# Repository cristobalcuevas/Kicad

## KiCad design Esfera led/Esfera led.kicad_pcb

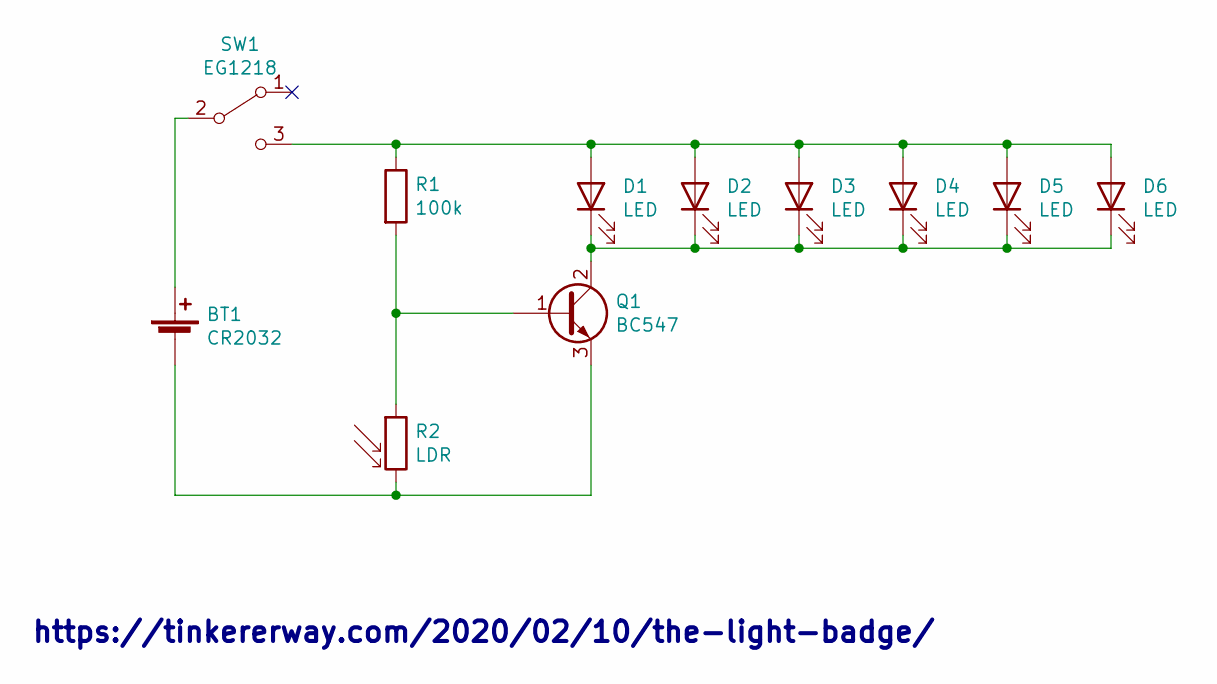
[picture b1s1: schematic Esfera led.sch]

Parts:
BT1: CR2032; BatteryHolder_Keystone_1058_1x2032
D1, D2, D3, D4, D5, D6: LED; LED_1206_3216Metric_Pad1.42x1.75mm_HandSolder
Q1: BC547; TO-92L_Inline
R1: 100k; R_1206_3216Metric_Pad1.42x1.75mm_HandSolder
R2: LDR; R_LDR_5.1x4.3mm_P3.4mm_Vertical
SW1: EG1218

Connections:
unnamed: BT1.1 (+), SW1.2 (B)
unnamed: BT1.2 (-), Q1.3 (E), R2.2
unnamed: D1.1 (K), D2.1 (K), D3.1 (K), D4.1 (K), D5.1 (K), D6.1 (K), Q1.2 (C)
unnamed: D1.2 (A), D2.2 (A), D3.2 (A), D4.2 (A), D5.2 (A), D6.2 (A), R1.1, SW1.3 (C)
unnamed: Q1.1 (B), R1.2, R2.1

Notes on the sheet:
https://tinkererway.com/2020/02/10/the-light-badge/

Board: 2 copper layers, 11 parts (1 on the bottom side), 5 nets, no tracks yet.

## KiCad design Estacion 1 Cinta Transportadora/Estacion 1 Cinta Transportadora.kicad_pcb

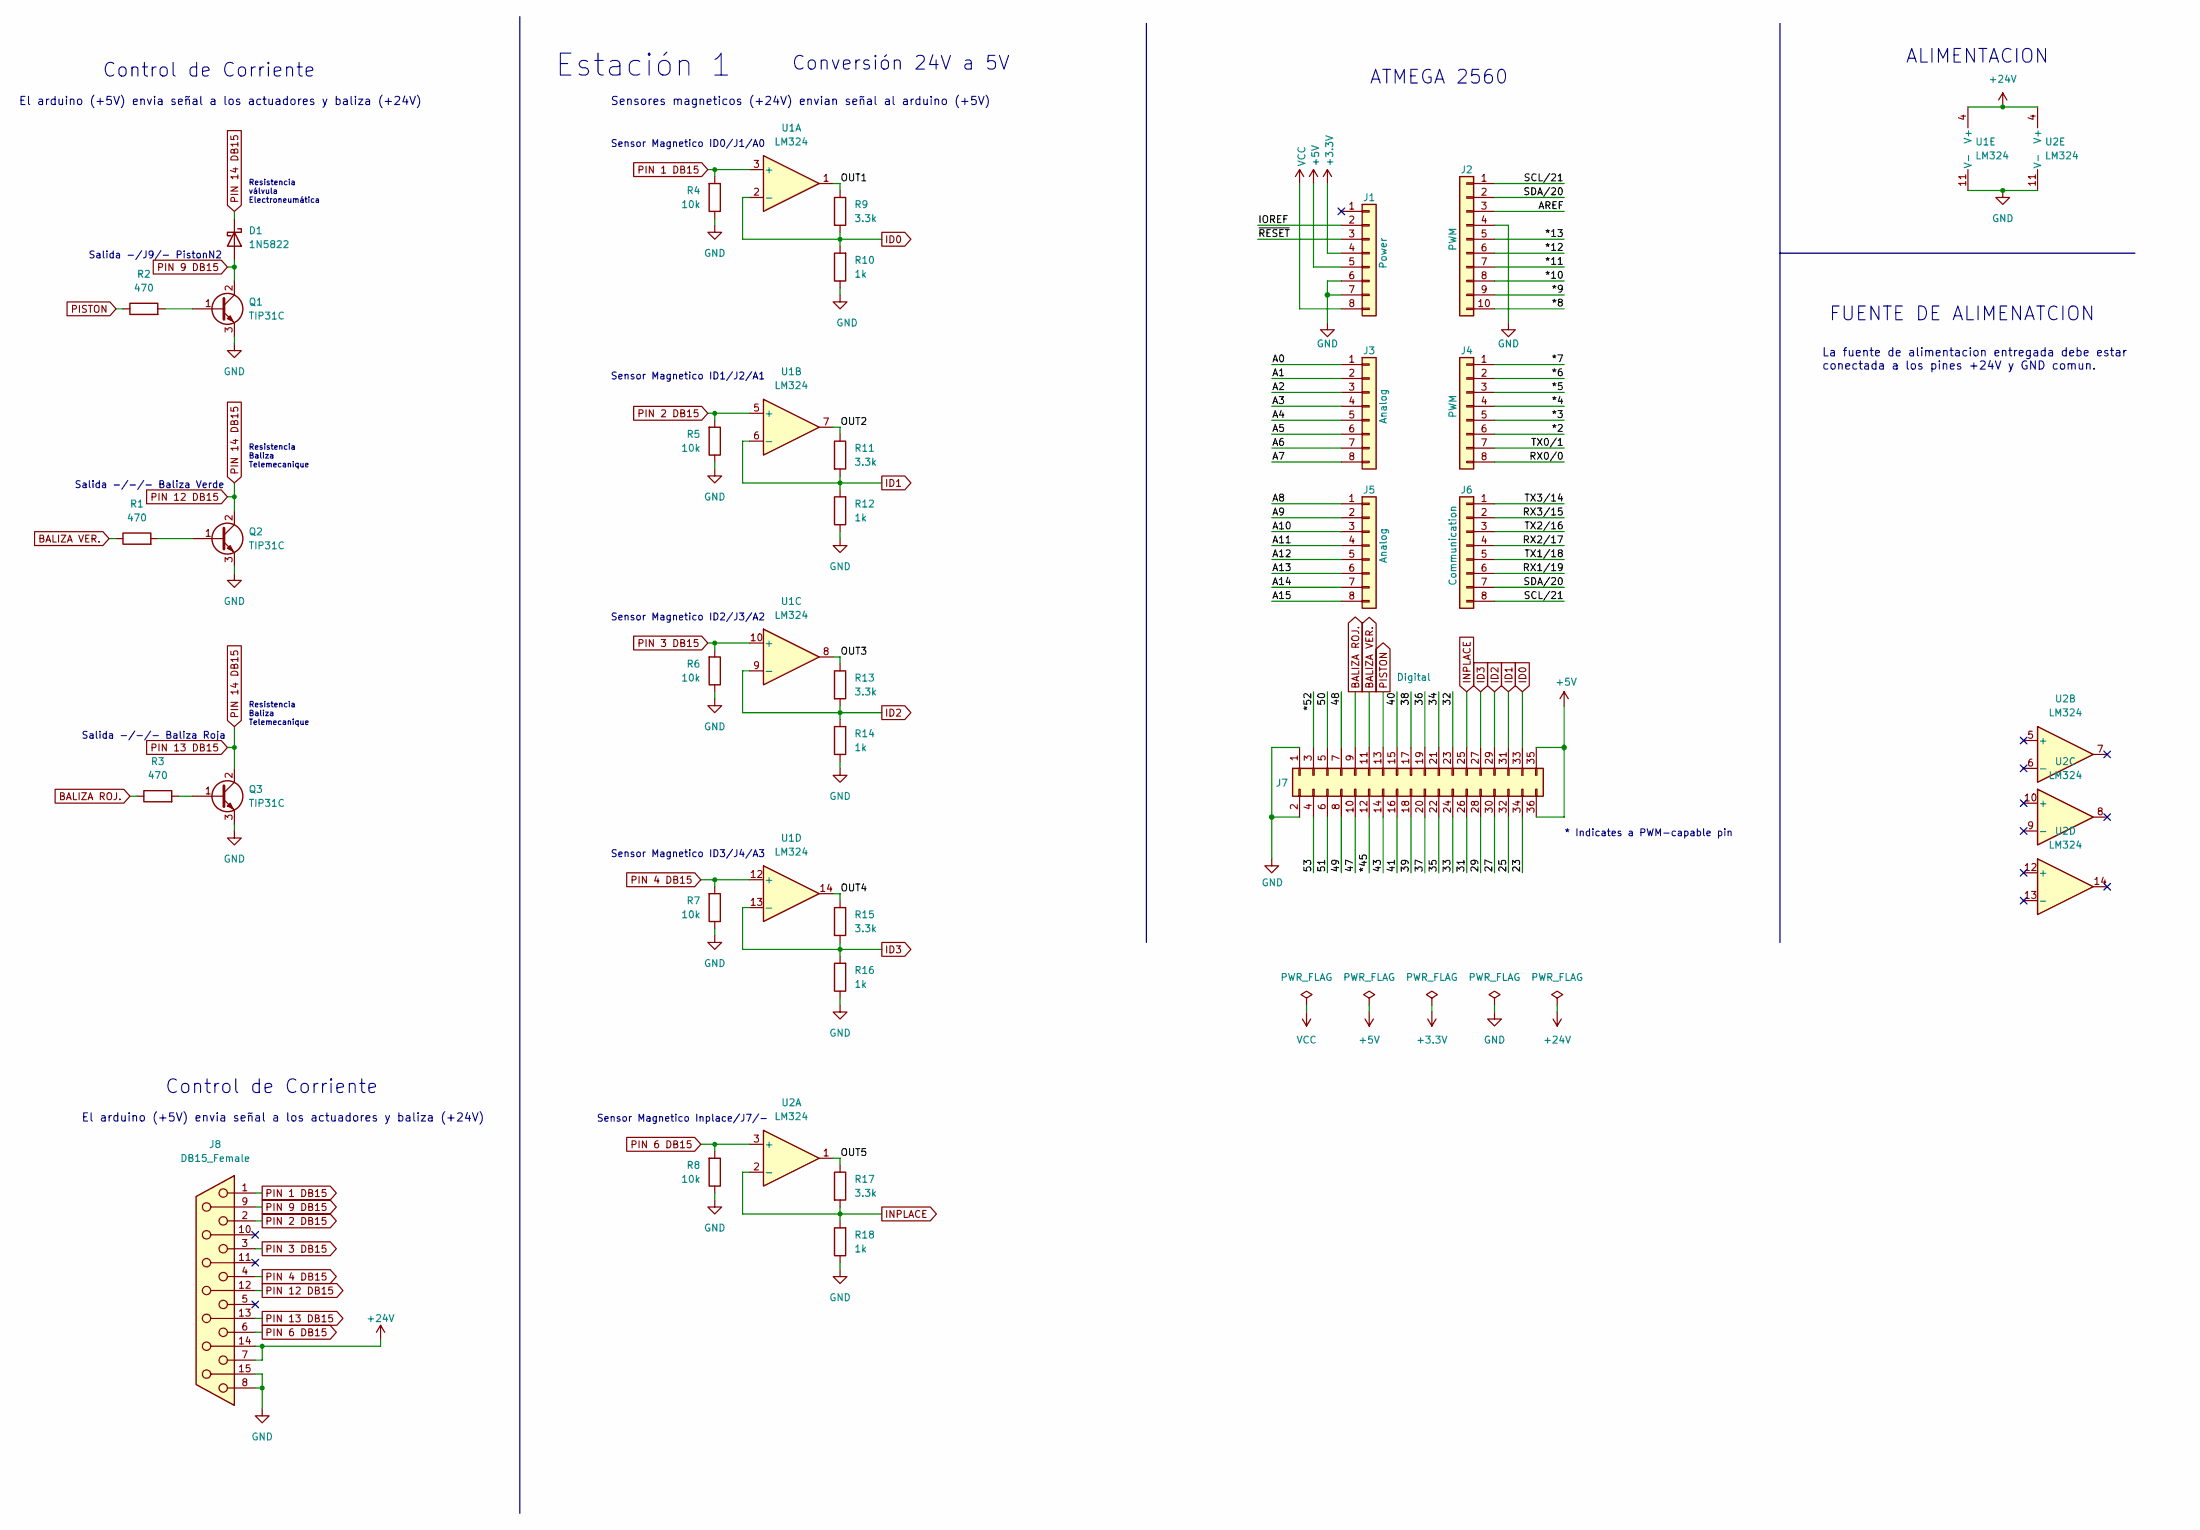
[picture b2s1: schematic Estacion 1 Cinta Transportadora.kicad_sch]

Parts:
D1: 1N5822; D_DO-201AD_P15.24mm_Horizontal
J1: Power; PinSocket_1x08_P2.54mm_Vertical
J2: PWM; PinSocket_1x10_P2.54mm_Vertical
J3, J5: Analog; PinSocket_1x08_P2.54mm_Vertical
J4: PWM; PinSocket_1x08_P2.54mm_Vertical
J6: Communication; PinSocket_1x08_P2.54mm_Vertical
J7: Digital; PinSocket_2x18_P2.54mm_Vertical
J8: DB15_Female; DSUB-15_Female_Vertical_P2.77x2.84mm
Q1, Q2, Q3: TIP31C; TO-220-3_Vertical
R1, R2, R3: 470; R_Axial_DIN0207_L6.3mm_D2.5mm_P10.16mm_Horizontal
R4, R5, R6, R7, R8: 10k; R_Axial_DIN0207_L6.3mm_D2.5mm_P10.16mm_Horizontal
R9, R11, R13, R15, R17: 3.3k; R_Axial_DIN0207_L6.3mm_D2.5mm_P10.16mm_Horizontal
R10, R12, R14, R16, R18: 1k; R_Axial_DIN0207_L6.3mm_D2.5mm_P10.16mm_Horizontal
U1, U2: LM324; DIP-14_W7.62mm

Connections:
+3V3: J1.4
+5V: J1.5, J7.35, J7.36
+24V: J8.7, J8.14, U1.4 (V+), U2.4 (V+)
/23: J7.34
/25: J7.32
/27: J7.30
/29: J7.28
/31: J7.26
/32: J7.23
/33: J7.24
/34: J7.21
/35: J7.22
/36: J7.19
/37: J7.20
/38: J7.17
/39: J7.18
/40: J7.15
/41: J7.16
/43: J7.14
/47: J7.10
/48: J7.7
/49: J7.8
/50: J7.5
/51: J7.6
/53: J7.4
/*2: J4.6
/*3: J4.5
/*4: J4.4
/*5: J4.3
/*6: J4.2
/*7: J4.1
/*8: J2.10
/*9: J2.9
/*10: J2.8
/*11: J2.7
/*12: J2.6
/*13: J2.5
/*45: J7.12
/*52: J7.3
/A0: J3.1
/A1: J3.2
/A2: J3.3
/A3: J3.4
/A4: J3.5
/A5: J3.6
/A6: J3.7
/A7: J3.8
/A8: J5.1
/A9: J5.2
/A10: J5.3
/A11: J5.4
/A12: J5.5
/A13: J5.6
/A14: J5.7
/A15: J5.8
/AREF: J2.3
/IOREF: J1.2
/OUT1: R9.1, U1.1
/OUT2: R11.1, U1.7
/OUT3: R13.1, U1.8
/OUT4: R15.1, U1.14
/OUT5: R17.1, U2.1
/RX0/0: J4.8
/RX1/19: J6.6
/RX2/17: J6.4
/RX3/15: J6.2
/SCL/21: J2.1, J6.8
/SDA/20: J2.2, J6.7
/TX0/1: J4.7
/TX1/18: J6.5
/TX2/16: J6.3
/TX3/14: J6.1
/~RESET: J1.3
BALIZA ROJ.: J7.9, R3.1
BALIZA VER.: J7.11, R1.1
GND: J1.6, J1.7, J2.4, J7.1, J7.2, J8.8, J8.15, Q1.3 (E), Q2.3 (E), Q3.3 (E), R4.1, R5.1, R6.1, R7.1, R8.1, R10.1, R12.1, R14.1, R16.1, R18.1, U1.11 (V-), U2.11 (V-)
ID0: J7.33, R9.2, R10.2, U1.2 (-)
ID1: J7.31, R11.2, R12.2, U1.6 (-)
ID2: J7.29, R13.2, R14.2, U1.9 (-)
ID3: J7.27, R15.2, R16.2, U1.13 (-)
INPLACE: J7.25, R17.2, R18.2, U2.2 (-)
unnamed: Q1.1 (B), R2.2
unnamed: Q2.1 (B), R1.2
unnamed: Q3.1 (B), R3.2
PIN 1 DB15: J8.1, R4.2, U1.3 (+)
PIN 2 DB15: J8.2, R5.2, U1.5 (+)
PIN 3 DB15: J8.3, R6.2, U1.10 (+)
PIN 4 DB15: J8.4, R7.2, U1.12 (+)
PIN 6 DB15: J8.6, R8.2, U2.3 (+)
PIN 9 DB15: D1.2 (A), J8.9, Q1.2 (C)
PIN 12 DB15: D1.1 (K), J8.12, J8.13, Q2.2 (C), Q3.2 (C)
PISTON: J7.13, R2.1
VCC: J1.8

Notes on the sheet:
Conversión 24V a 5V
Control de Corriente
Resistencia Baliza Telemecanique
Sensor Magnetico Inplace/J7/-
El arduino (+5V) envia señal a los actuadores y baliza (+24V)
Sensor Magnetico ID2/J3/A2
Sensor Magnetico ID1/J2/A1
Estación 1
Salida -/-/- Baliza Verde
Sensor Magnetico ID0/J1/A0
Salida -/-/- Baliza Roja
Sensores magneticos (+24V) envian señal al arduino (+5V)
Resistencia válvula Electroneumática
FUENTE DE ALIMENATCION
ATMEGA 2560
Salida -/J9/- PistonN2
Sensor Magnetico ID3/J4/A3
* Indicates a PWM-capable pin
ALIMENTACION
La fuente de alimentacion entregada debe estar conectada a los pines +24V y GND comun.

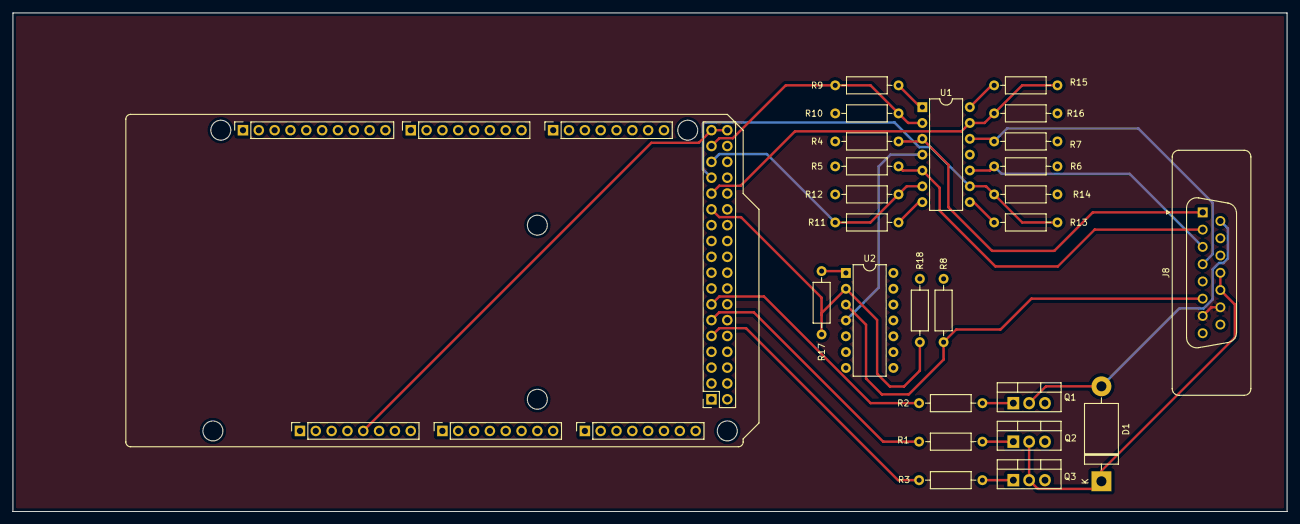
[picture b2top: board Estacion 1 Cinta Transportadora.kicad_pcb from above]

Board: 2 copper layers, 204.5 x 80.0 mm, 38 parts (0 on the bottom side), 28 nets.

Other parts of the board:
MH1, MH2, MH3, MH4, MH5, MH6: MountingHole_3.2mm

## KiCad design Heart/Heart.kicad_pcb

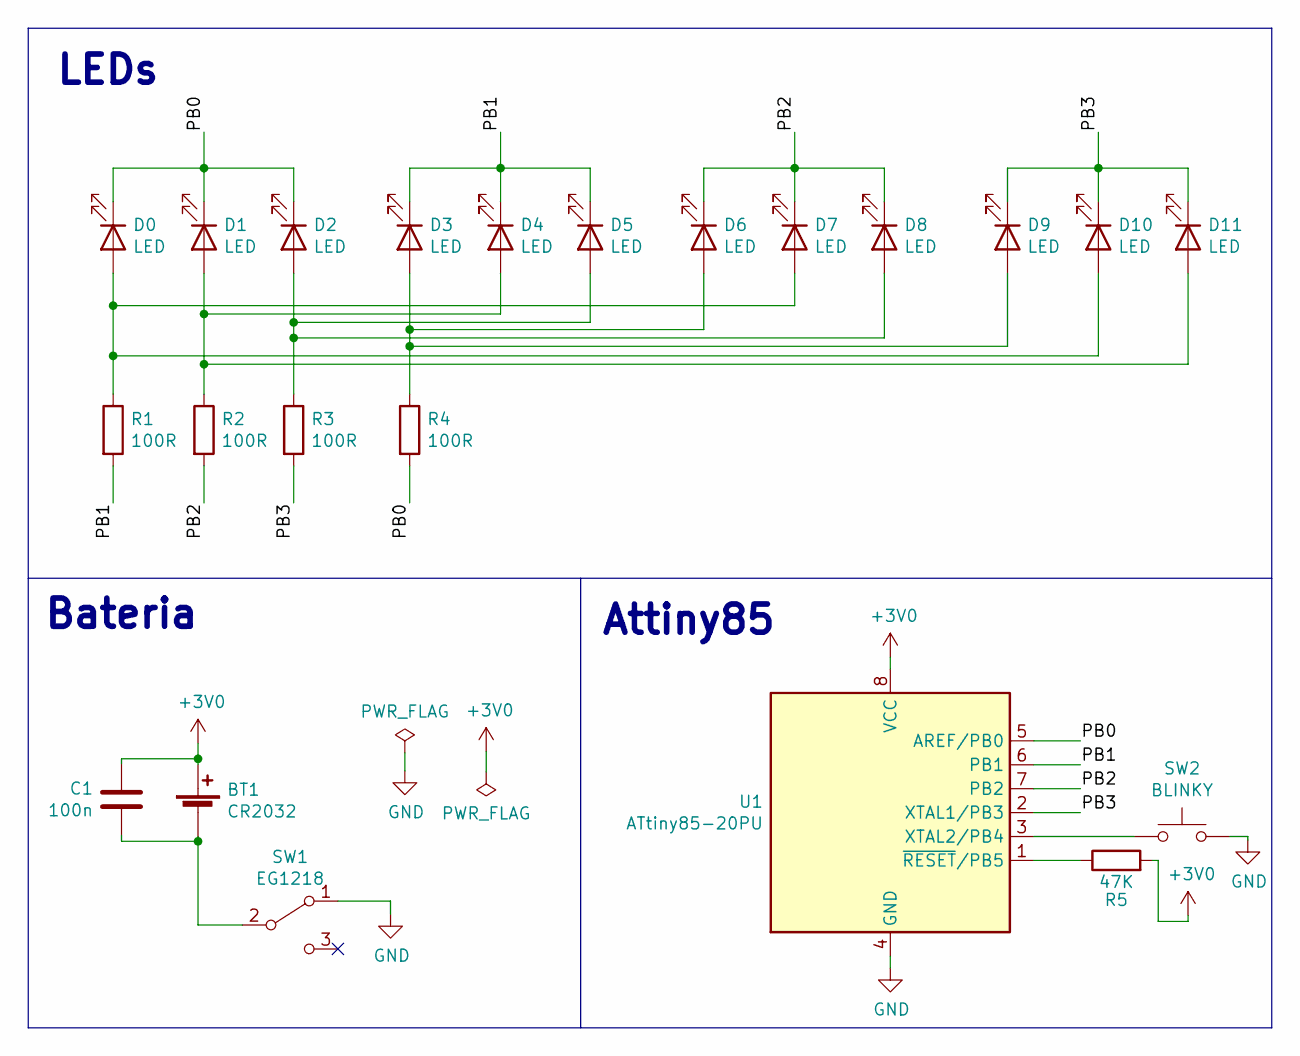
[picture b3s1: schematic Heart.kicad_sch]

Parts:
BT1: CR2032; Batteriehalter_CR2032
C1: 100n; C_0805_2012Metric_Pad1.15x1.40mm_HandSolder
D0, D1, D2, D3, D4, D5, D6, D7, D8, D9, D10, D11: LED; LED_D5.0mm
R1, R2, R3, R4: 100R; R_0805_2012Metric_Pad1.15x1.40mm_HandSolder
R5: 47K; R_0805_2012Metric_Pad1.15x1.40mm_HandSolder
SW1: EG1218; 3Pin_Sensor_SMD
SW2: BLINKY; Taster_SMD_eBay4,5x3mm
U1: ATtiny85-20PU; DIP-8_W7.62mm_Socket

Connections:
+3V0: BT1.1 (+), C1.2, R5.2, U1.8 (VCC)
/PB0: D0.1 (K), D1.1 (K), D2.1 (K), R4.2, U1.5 (AREF/PB0)
/PB1: D3.1 (K), D4.1 (K), D5.1 (K), R1.2, U1.6 (PB1)
/PB2: D6.1 (K), D7.1 (K), D8.1 (K), R2.2, U1.7 (PB2)
/PB3: D9.1 (K), D10.1 (K), D11.1 (K), R3.2, U1.2 (XTAL1/PB3)
GND: SW1.1 (A), SW2.2, U1.4 (GND)
unnamed: BT1.2 (-), C1.1, SW1.2 (B)
unnamed: D0.2 (A), D7.2 (A), D10.2 (A), R1.1
unnamed: D1.2 (A), D4.2 (A), D11.2 (A), R2.1
unnamed: D2.2 (A), D5.2 (A), D8.2 (A), R3.1
unnamed: D3.2 (A), D6.2 (A), D9.2 (A), R4.1
unnamed: R5.1, U1.1 (~RESET/PB5)
unnamed: SW2.1, U1.3 (XTAL2/PB4)

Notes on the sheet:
LEDs
Bateria
Attiny85

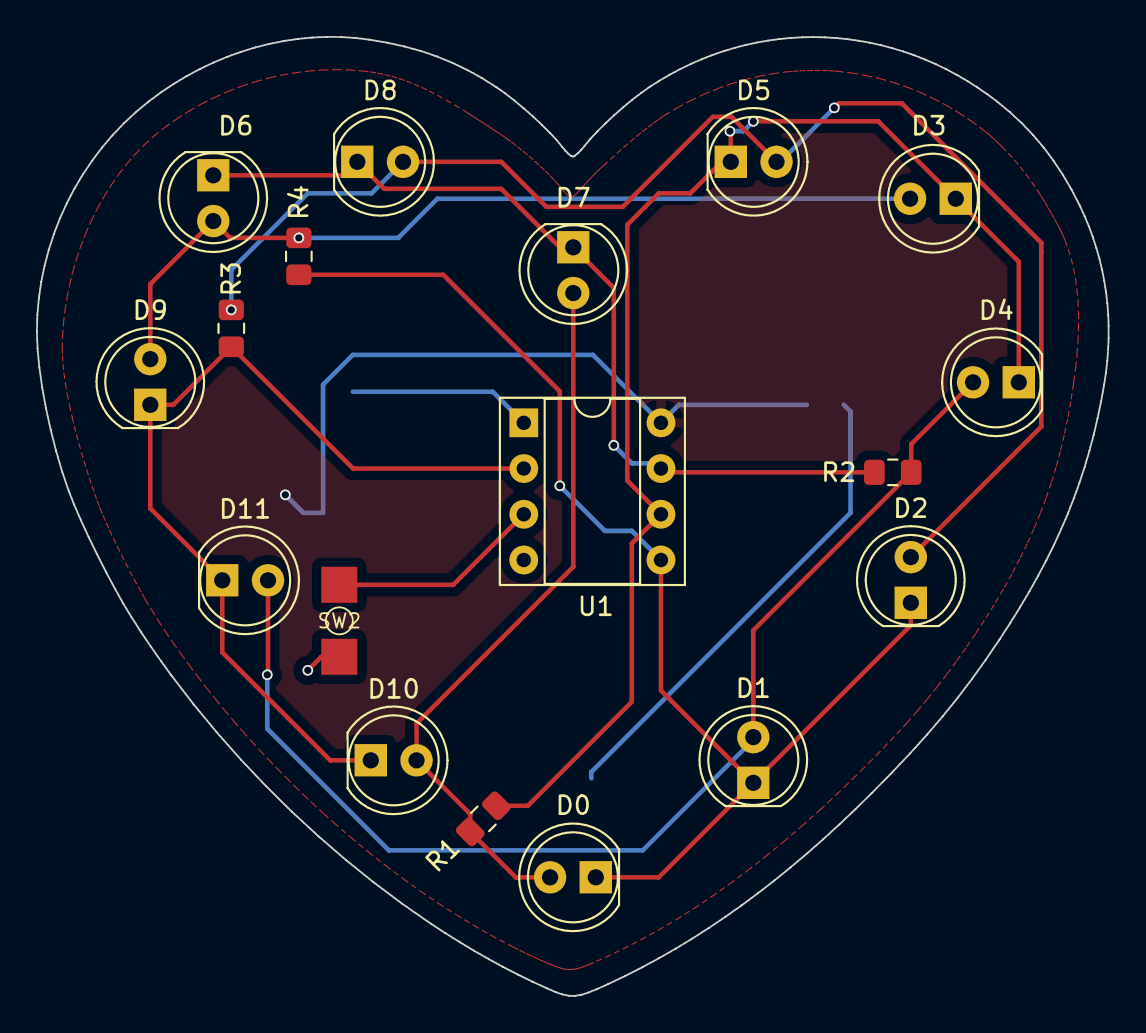
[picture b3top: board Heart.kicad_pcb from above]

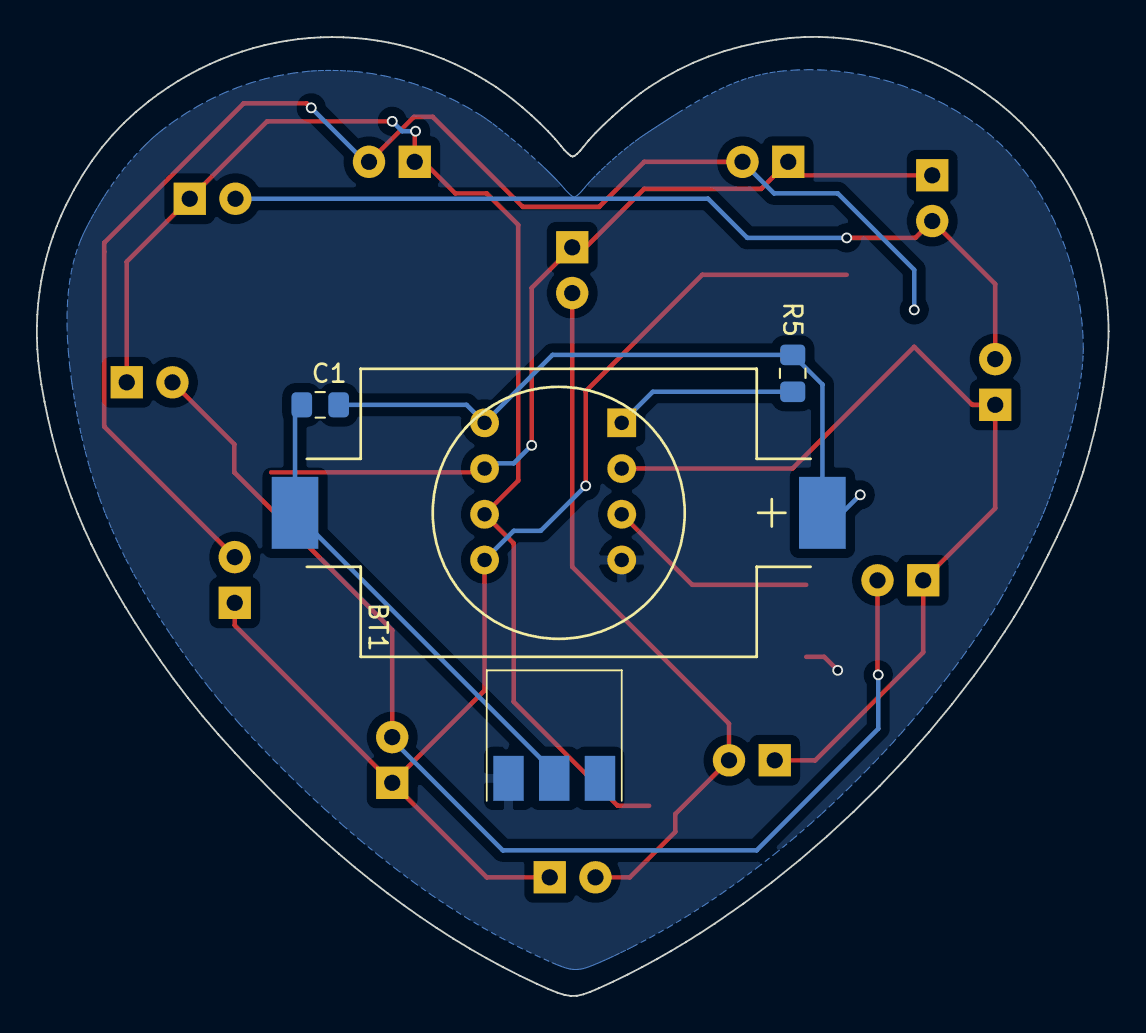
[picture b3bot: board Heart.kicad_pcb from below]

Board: 2 copper layers, 59.5 x 53.3 mm, 22 parts (4 on the bottom side), 13 nets.

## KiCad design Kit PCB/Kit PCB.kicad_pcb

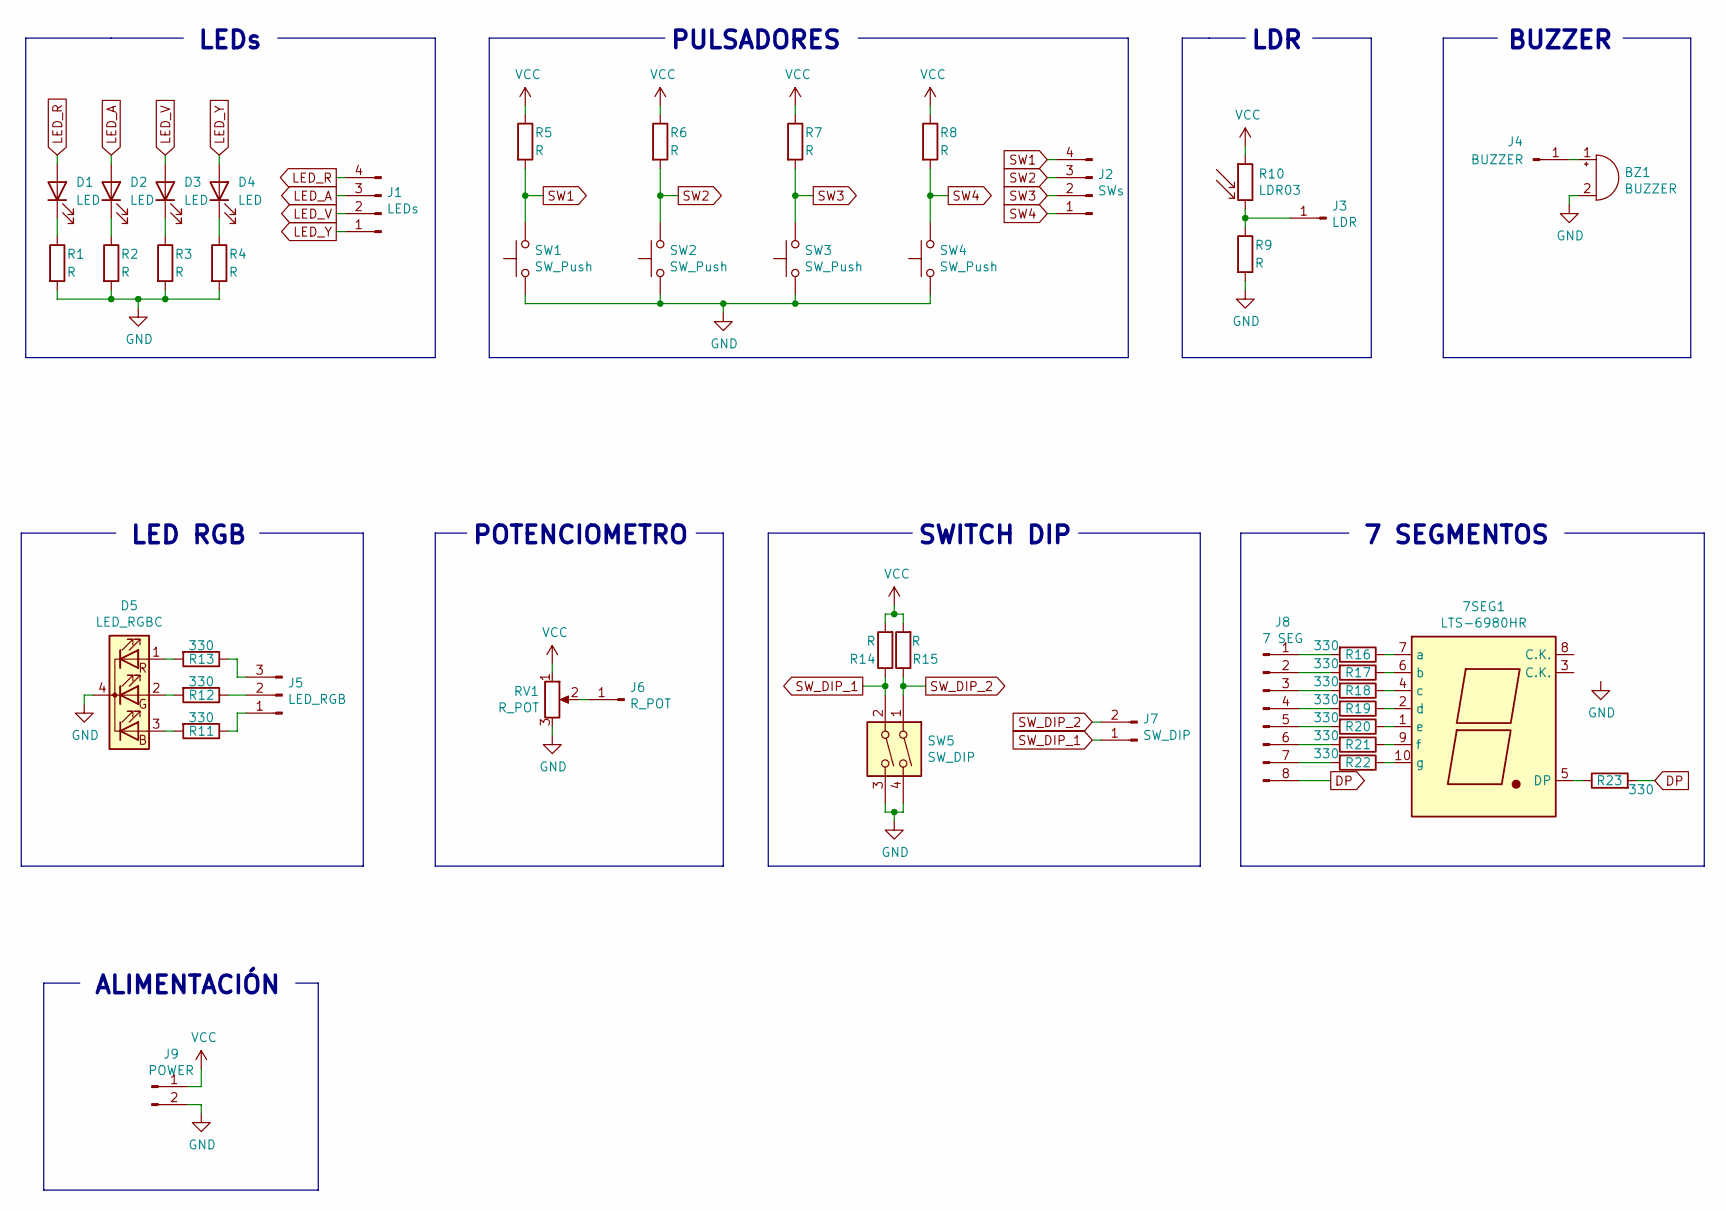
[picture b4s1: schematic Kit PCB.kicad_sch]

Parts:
7SEG1: LTS-6980HR; 7SegmentLED_LTS6760_LTS6780
BZ1: BUZZER; Buzzer_TDK_PS1240P02BT_D12.2mm_H6.5mm
D1, D2, D3, D4: LED; LED_D5.0mm
D5: LED_RGBC; LED_D5.0mm-4_RGB_Staggered_Pins
J1: LEDs; PinHeader_1x04_P2.54mm_Vertical
J2: SWs; PinHeader_1x04_P2.54mm_Vertical
J3: LDR; PinHeader_1x01_P2.54mm_Vertical
J4: BUZZER; PinHeader_1x01_P2.54mm_Vertical
J5: LED_RGB; PinHeader_1x03_P2.54mm_Vertical
J6: R_POT; PinHeader_1x01_P2.54mm_Vertical
J7: SW_DIP; PinHeader_1x02_P2.54mm_Vertical
J8: 7 SEG; PinHeader_1x08_P2.54mm_Vertical
J9: POWER; PinHeader_1x02_P2.54mm_Vertical
R1, R2, R3, R4, R5, R6, R7, R8, R9, R14, R15: R; R_Axial_DIN0207_L6.3mm_D2.5mm_P7.62mm_Horizontal
R10: LDR03; R_LDR_5.1x4.3mm_P3.4mm_Vertical
R11, R12, R13, R16, R17, R18, R19, R20, R21, R22, R23: 330; R_Axial_DIN0207_L6.3mm_D2.5mm_P7.62mm_Horizontal
RV1: R_POT; PinHeader_1x03_P2.54mm_Vertical
SW1, SW2, SW3, SW4: SW_Push; SW_PUSH_6mm
SW5: SW_DIP; SW_DIP_SPSTx02_Slide_9.78x7.26mm_W7.62mm_P2.54mm

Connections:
DP: J8.8, R23.2
GND: BZ1.2 (+), D5.4 (K), J9.2, R1.2, R2.2, R3.2, R4.2, R9.2, RV1.3, SW1.1, SW2.1, SW3.1, SW4.1, SW5.3, SW5.4
LED_A: D2.2 (A), J1.3
LED_R: D1.2 (A), J1.4
LED_V: D3.2 (A), J1.2
LED_Y: D4.2 (A), J1.1
unnamed: 7SEG1.1 (e), R20.1
unnamed: 7SEG1.2 (d), R19.1
unnamed: 7SEG1.4 (c), R18.1
unnamed: 7SEG1.5 (DP), R23.1
unnamed: 7SEG1.6 (b), R17.1
unnamed: 7SEG1.7 (a), R16.1
unnamed: 7SEG1.9 (f), R21.1
unnamed: 7SEG1.10 (g), R22.1
unnamed: BZ1.1 (-), J4.1
unnamed: D1.1 (K), R1.1
unnamed: D2.1 (K), R2.1
unnamed: D3.1 (K), R3.1
unnamed: D4.1 (K), R4.1
unnamed: D5.1 (RA), R13.2
unnamed: D5.2 (GA), R12.2
unnamed: D5.3 (BA), R11.2
unnamed: J3.1, R9.1, R10.2
unnamed: J5.1, R11.1
unnamed: J5.2, R12.1
unnamed: J5.3, R13.1
unnamed: J6.1, RV1.2
unnamed: J8.1, R16.2
unnamed: J8.2, R17.2
unnamed: J8.3, R18.2
unnamed: J8.4, R19.2
unnamed: J8.5, R20.2
unnamed: J8.6, R21.2
unnamed: J8.7, R22.2
SW1: J2.4, R5.2, SW1.2
SW2: J2.3, R6.2, SW2.2
SW3: J2.2, R7.2, SW3.2
SW4: J2.1, R8.2, SW4.2
SW_DIP_1: J7.1, R14.1, SW5.2
SW_DIP_2: J7.2, R15.1, SW5.1
VCC: J9.1, R5.1, R6.1, R7.1, R8.1, R10.1, R14.2, R15.2, RV1.1

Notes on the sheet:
SWITCH DIP
BUZZER
LDR
LED RGB
7 SEGMENTOS
LEDs
ALIMENTACIÓN
PULSADORES
POTENCIOMETRO

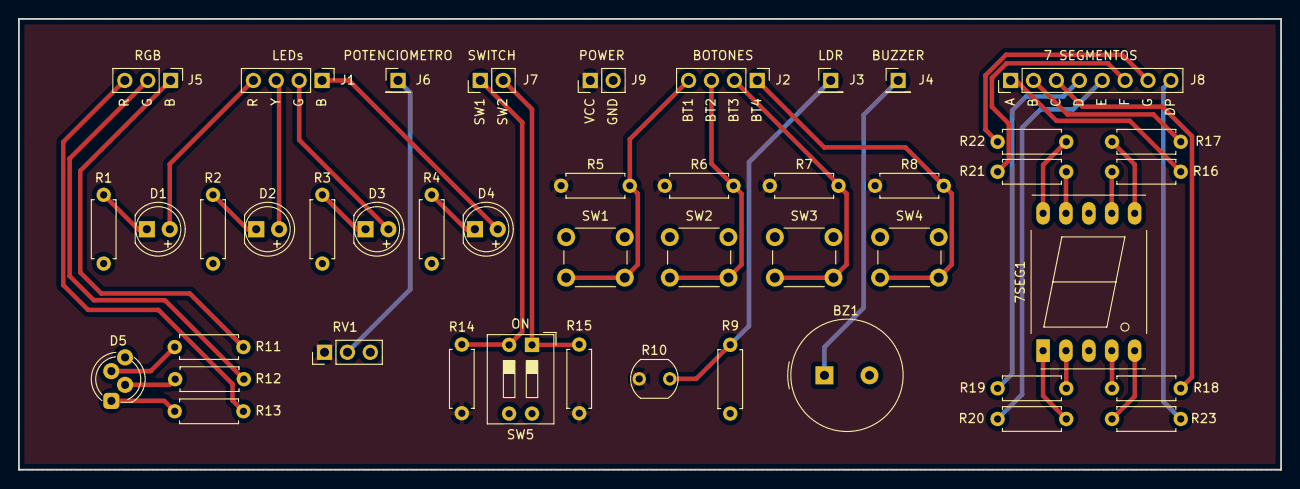
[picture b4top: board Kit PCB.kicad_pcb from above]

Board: 2 copper layers, 140.0 x 50.0 mm, 45 parts (0 on the bottom side), 41 nets.

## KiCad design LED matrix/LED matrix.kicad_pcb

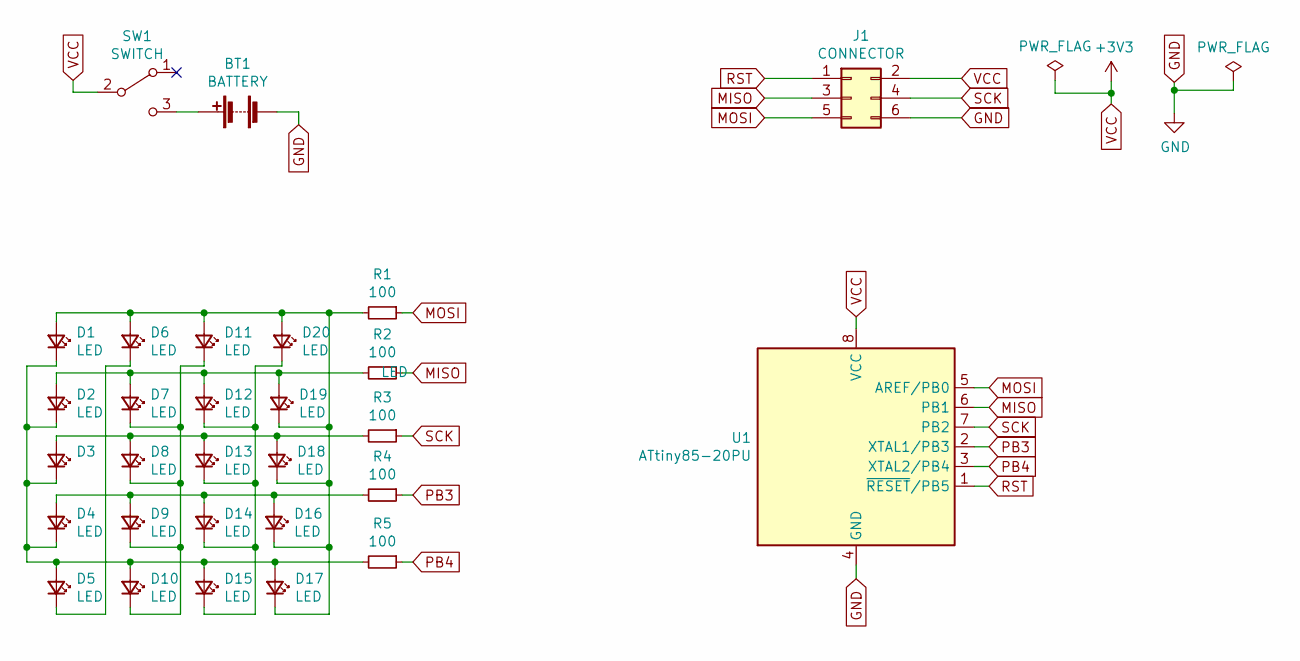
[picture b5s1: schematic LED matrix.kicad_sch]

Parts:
BT1: BATTERY; BatteryHolder_Keystone_103_1x20mm
D1, D2, D3, D4, D5, D6, D7, D8, D9, D10, D11, D12, D13, D14, D15, D16, D17, D18, D19, D20: LED; LED_D3.0mm
J1: CONNECTOR; PinHeader_2x03_P2.54mm_Vertical
R1, R2, R3, R4, R5: 100; R_Axial_DIN0204_L3.6mm_D1.6mm_P5.08mm_Horizontal
SW1: SWITCH; SW_CuK_JS202011CQN_DPDT_Straight
U1: ATtiny85-20PU; DIP-8_W7.62mm

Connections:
GND: BT1.2 (-), J1.6, U1.4 (GND)
MISO: J1.3, R2.1, U1.6 (PB1)
MOSI: J1.5, R1.1, U1.5 (AREF/PB0)
unnamed: BT1.1 (+), SW1.3 (C)
unnamed: D1.1 (K), D2.1 (K), D3.1 (K), D4.1 (K), D5.2 (A), D10.2 (A), D15.2 (A), D17.2 (A), R5.2
unnamed: D1.2 (A), D6.2 (A), D11.2 (A), D16.1 (K), D17.1 (K), D18.1 (K), D19.1 (K), D20.2 (A), R1.2
unnamed: D5.1 (K), D6.1 (K)
unnamed: D7.1 (K), D8.1 (K), D9.1 (K), D10.1 (K), D11.1 (K)
unnamed: D12.1 (K), D13.1 (K), D14.1 (K), D15.1 (K), D20.1 (K)
unnamed: D2.2 (A), D7.2 (A), D12.2 (A), D19.2 (A), R2.2
unnamed: D3.2 (A), D8.2 (A), D13.2 (A), D18.2 (A), R3.2
unnamed: D4.2 (A), D9.2 (A), D14.2 (A), D16.2 (A), R4.2
PB3: R4.1, U1.2 (XTAL1/PB3)
PB4: R5.1, U1.3 (XTAL2/PB4)
RST: J1.1, U1.1 (~RESET/PB5)
SCK: J1.4, R3.1, U1.7 (PB2)
VCC: J1.2, SW1.2 (B), U1.8 (VCC)

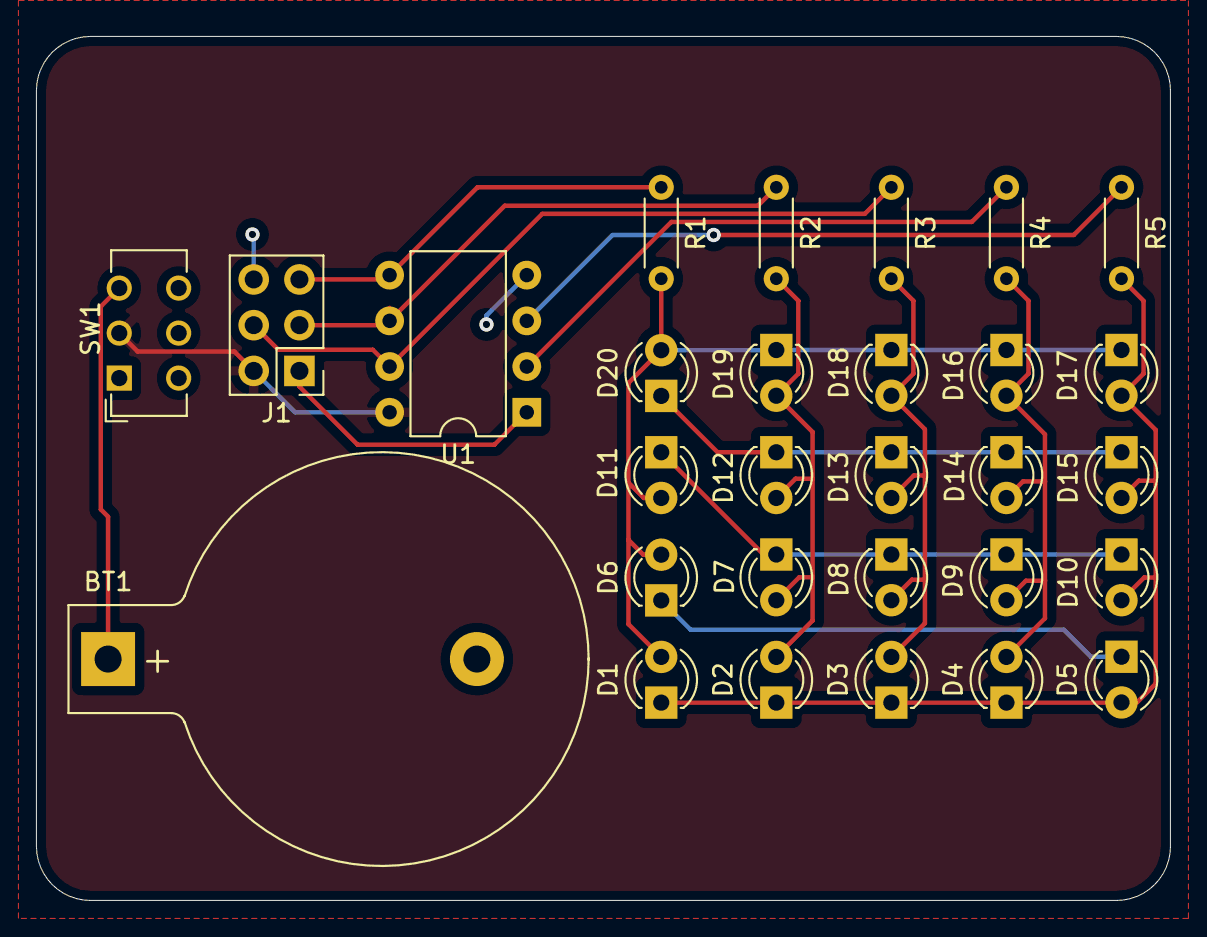
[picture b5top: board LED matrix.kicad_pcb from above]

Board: 2 copper layers, 63.0 x 48.0 mm, 29 parts (0 on the bottom side), 17 nets.

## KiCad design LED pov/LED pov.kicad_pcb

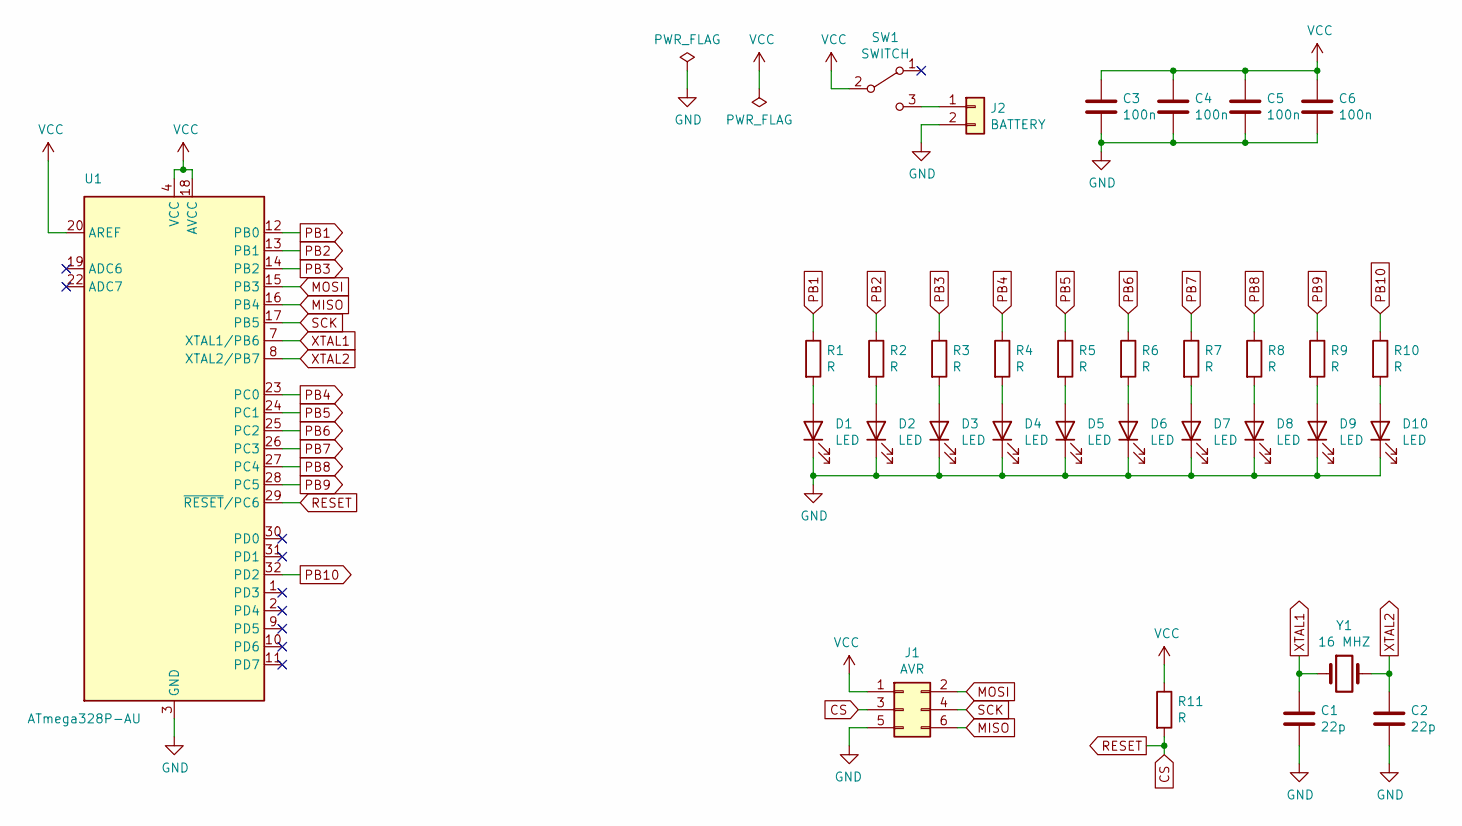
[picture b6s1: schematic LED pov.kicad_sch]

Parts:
C1, C2: 22p; C_1206_3216Metric
C3, C4, C5, C6: 100n; C_1206_3216Metric
D1, D2, D3, D4, D5, D6, D7, D8, D9, D10: LED; LED_1206_3216Metric
J1: AVR; PinHeader_2x03_P2.54mm_Vertical
J2: BATTERY; PinHeader_1x02_P2.54mm_Vertical
R1, R2, R3, R4, R5, R6, R7, R8, R9, R10, R11: R; R_1206_3216Metric
SW1: SWITCH; SW_SPDT_PCM12
U1: ATmega328P-AU; TQFP-32_7x7mm_P0.8mm
Y1: 16 MHZ; Crystal_HC49-4H_Vertical

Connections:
CS: J1.3, R11.2, U1.29 (~RESET/PC6)
GND: C1.2, C2.2, C3.2, C4.2, C5.2, C6.2, D1.1 (K), D2.1 (K), D3.1 (K), D4.1 (K), D5.1 (K), D6.1 (K), D7.1 (K), D8.1 (K), D9.1 (K), D10.1 (K), J1.5, J2.2, U1.3 (GND), U1.5 (GND), U1.21 (GND)
MISO: J1.6, U1.16 (PB4)
MOSI: J1.2, U1.15 (PB3)
unnamed: D1.2 (A), R1.2
unnamed: D2.2 (A), R2.2
unnamed: D3.2 (A), R3.2
unnamed: D4.2 (A), R4.2
unnamed: D5.2 (A), R5.2
unnamed: D6.2 (A), R6.2
unnamed: D7.2 (A), R7.2
unnamed: D8.2 (A), R8.2
unnamed: D9.2 (A), R9.2
unnamed: D10.2 (A), R10.2
unnamed: J2.1, SW1.3 (C)
PB1: R1.1, U1.12 (PB0)
PB2: R2.1, U1.13 (PB1)
PB3: R3.1, U1.14 (PB2)
PB4: R4.1, U1.23 (PC0)
PB5: R5.1, U1.24 (PC1)
PB6: R6.1, U1.25 (PC2)
PB7: R7.1, U1.26 (PC3)
PB8: R8.1, U1.27 (PC4)
PB9: R9.1, U1.28 (PC5)
PB10: R10.1, U1.32 (PD2)
SCK: J1.4, U1.17 (PB5)
VCC: C3.1, C4.1, C5.1, C6.1, J1.1, R11.1, SW1.2 (B), U1.4 (VCC), U1.6 (VCC), U1.18 (AVCC), U1.20 (AREF)
XTAL1: C1.1, U1.7 (XTAL1/PB6), Y1.1
XTAL2: C2.1, U1.8 (XTAL2/PB7), Y1.2

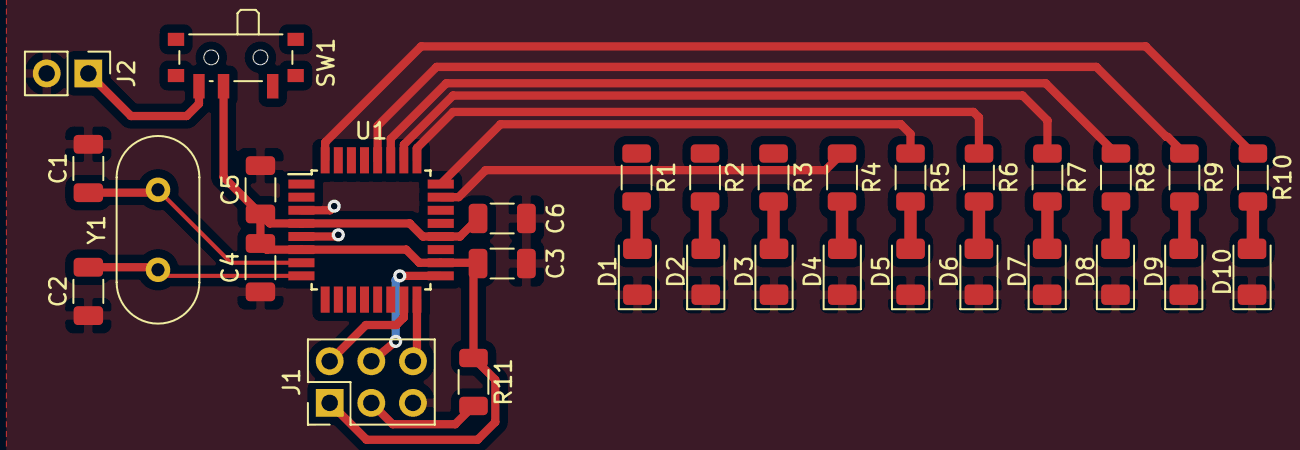
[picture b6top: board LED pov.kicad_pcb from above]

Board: 2 copper layers, 32 parts (0 on the bottom side), 29 nets.
